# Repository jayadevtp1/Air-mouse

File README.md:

# Air Mouse

Air mouse using Esp32

Four button and a joystick 

mpu6050 

lipo battery charging circuit

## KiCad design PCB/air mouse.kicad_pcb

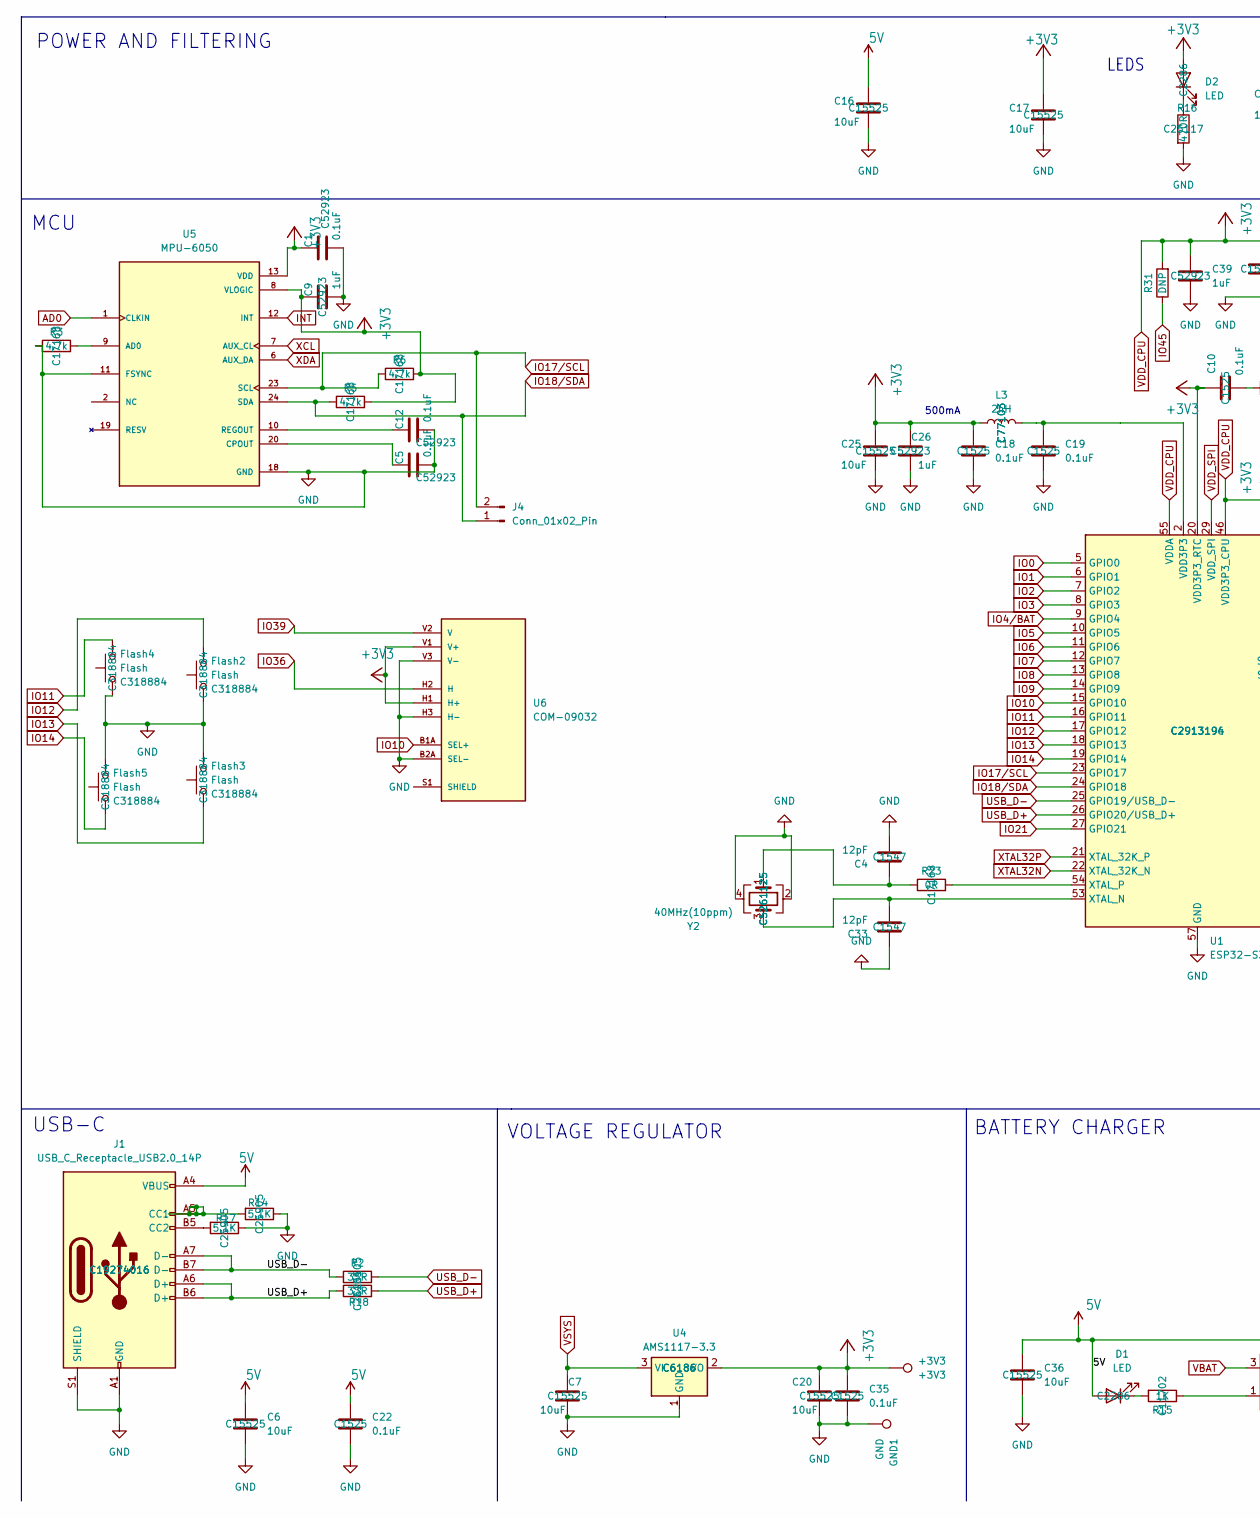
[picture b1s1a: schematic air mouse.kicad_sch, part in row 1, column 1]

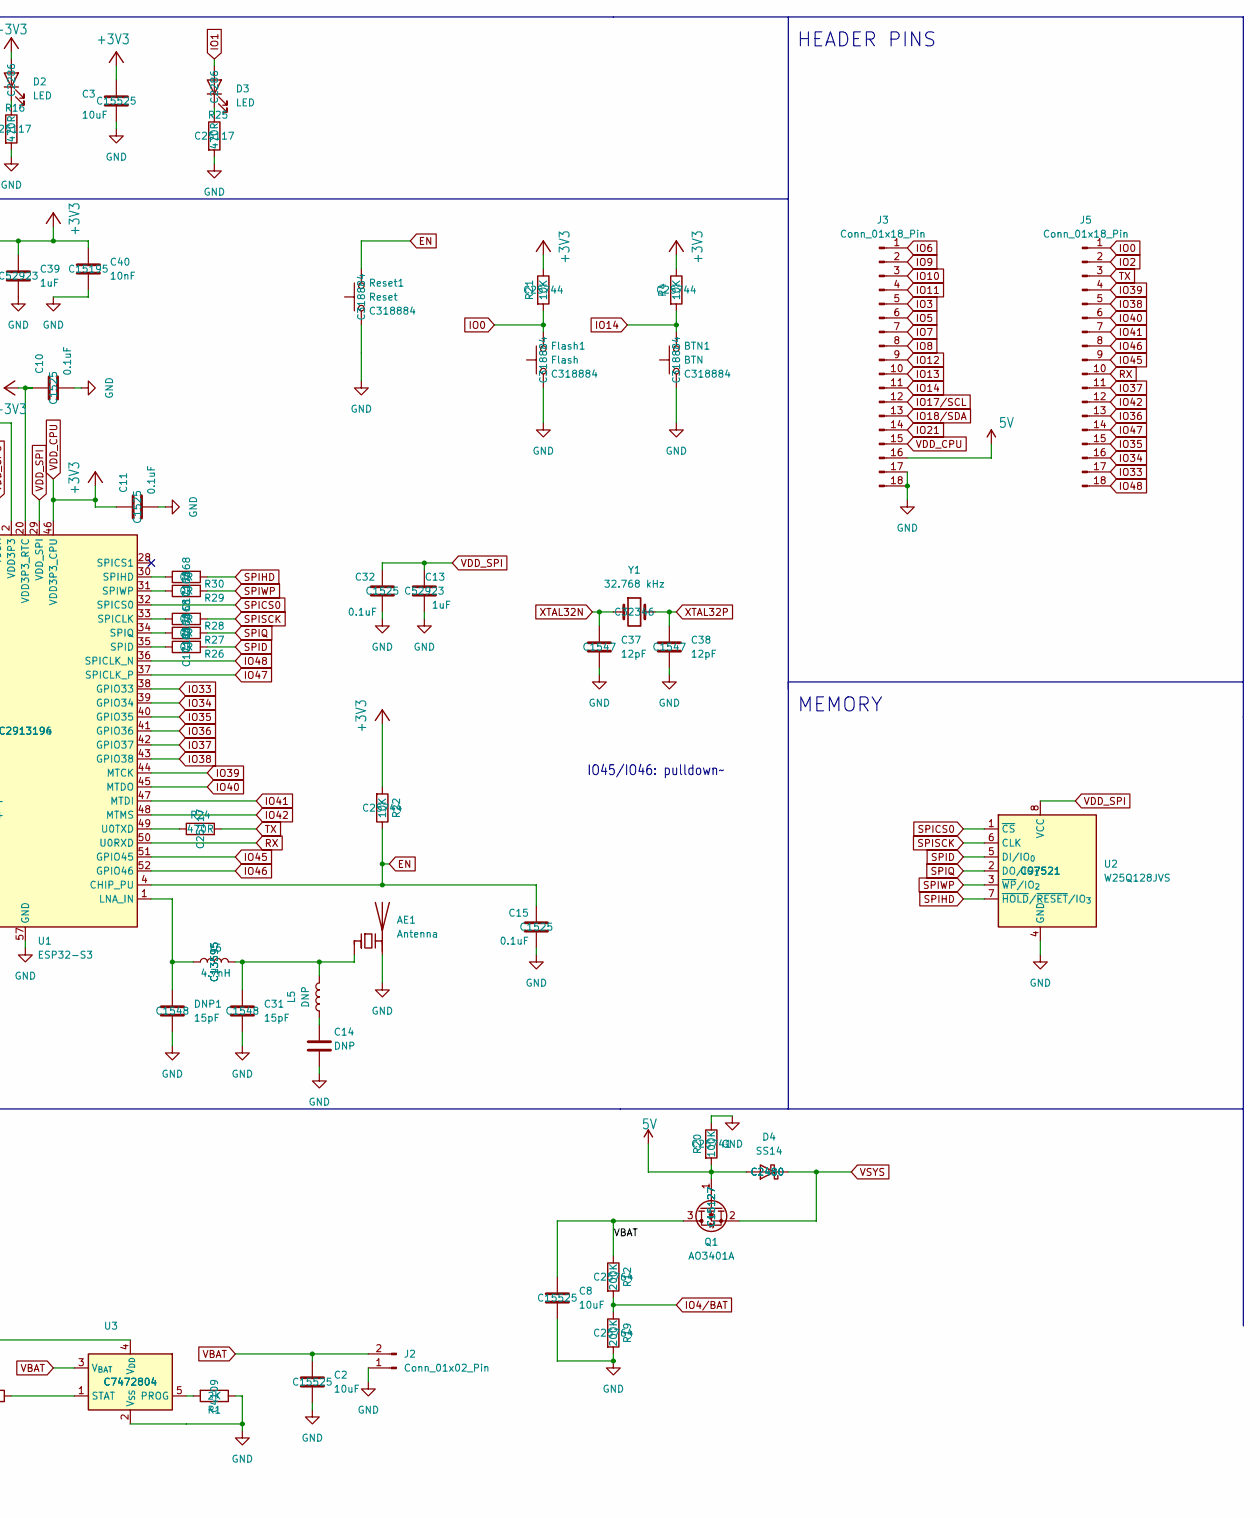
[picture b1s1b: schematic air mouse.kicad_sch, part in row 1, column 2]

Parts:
+3V3: +3V3; TestPoint_Pad_D1.0mm
AE1: Antenna; Texas_SWRA117D_2.4GHz_Left
BTN1: BTN; SW_Push_1P1T_XKB_TS-1187A; MNF PART NUMBER C318884; LCSC C318884
C1, C5, C12: 0.1uF; C_0402_1005Metric; MNF PART NUMBER C52923; LCSC C52923
C2, C3, C6, C7, C8, C16, C17, C20, C25, C36: 10uF; C_0402_1005Metric; MNF PART NUMBER C15525; LCSC C15525
C4, C33, C37, C38: 12pF; C_0402_1005Metric; MNF PART NUMBER C1547; LCSC C1547
C9, C13, C26, C39: 1uF; C_0402_1005Metric; MNF PART NUMBER C52923; LCSC C52923
C10, C11, C15, C18, C19, C22, C32, C35: 0.1uF; C_0402_1005Metric; MNF PART NUMBER C1525; LCSC C1525
C14: DNP; C_0402_1005Metric
C31: 15pF; C_0402_1005Metric; MNF PART NUMBER C1548; LCSC C1548
C40: 10nF; C_0402_1005Metric; MNF PART NUMBER C15195; LCSC C15195
D1, D2, D3: LED; LED_0603_1608Metric; MNF PART NUMBER C2286; LCSC C2286
D4: SS14; D_SMA; MNF PART NUMBER C2480; LCSC C2480
DNP1: 15pF; C_0402_1005Metric; MNF PART NUMBER C1548; LCSC C1548
Flash1, Flash2, Flash3, Flash4, Flash5: Flash; SW_Push_1P1T_XKB_TS-1187A; MNF PART NUMBER C318884; LCSC C318884
GND1: GND; TestPoint_Pad_D1.0mm
J1: USB_C_Receptacle_USB2.0_14P; USB_C_Receptacle_HCTL_HC-TYPE-C-16P-01A; MNF PART NUMBER C19274016; LCSC C19274016
J2, J4: Conn_01x02_Pin; PinSocket_1x02_P2.54mm_Vertical
J3, J5: Conn_01x18_Pin; PinHeader_1x18_P2.54mm_Vertical
L3: 2nH; L_0402_1005Metric; MNF PART NUMBER C77103; LCSC C77103
L5: DNP; L_0402_1005Metric
L6: 4.7nH; L_0402_1005Metric; MNF PART NUMBER C13595; LCSC C13595
Q1: AO3401A; SOT-23; MNF PART NUMBER C15127; LCSC C15127
R1: 2K; R_0402_1005Metric; MNF PART NUMBER C4109; LCSC C4109
R2, R18: 33R; R_0402_1005Metric; MNF PART NUMBER C25105; LCSC C25105
R3, R5, R6: 4.7k; R_0402_1005Metric; MNF PART NUMBER C17168; LCSC C17168
R4, R21, R22: 10K; R_0402_1005Metric; MNF PART NUMBER C25744; LCSC C25744
R12, R19: 200K; R_0402_1005Metric; MNF PART NUMBER C25764; LCSC C25764
R14, R17: 5.1K; R_0402_1005Metric; MNF PART NUMBER C25905; LCSC C25905
R15: 1K; R_0402_1005Metric; MNF PART NUMBER C11702; LCSC C11702
R16, R24, R25: 470R; R_0402_1005Metric; MNF PART NUMBER C25117; LCSC C25117
R20: 100K; R_0402_1005Metric; MNF PART NUMBER C25741; LCSC C25741
R23, R26, R27, R28, R29, R30: 0R; R_0402_1005Metric; MNF PART NUMBER C17168; LCSC C17168
R31: DNP; R_0402_1005Metric
Reset1: Reset; SW_Push_1P1T_XKB_TS-1187A; MNF PART NUMBER C318884; LCSC C318884
U1: ESP32-S3; QFN-56-1EP_7x7mm_P0.4mm_EP4x4mm; MNF PART NUMBER C2913196; LCSC C2913194
U2: W25Q128JVS; SOIC-8_5.3x5.3mm_P1.27mm; MNF PART NUMBER C97521; LCSC C97521
U3: MCP73831-2-OT; SOT-23-5; MNF PART NUMBER C7472804; LCSC C7472804
U4: AMS1117-3.3; SOT-223-3_TabPin2; MNF PART NUMBER C6186; LCSC C6186
U5: MPU-6050; QFN50P400X400X95-24N; PARTREV 3.4
U6: COM-09032; XDCR_COM-09032; PARTREV N/A
Y1: 32.768 kHz; Crystal_SMD_3215-2Pin_3.2x1.5mm; MNF PART NUMBER C32346; LCSC C32346
Y2: 40MHz(10ppm); Crystal_SMD_2520-4Pin_2.5x2.0mm; MNF PART NUMBER C5261125; LCSC C5261125

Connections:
5V: C6.1, C16.1, C22.1, C36.1, D1.2 (A), D4.2 (A), J1.A4 (VBUS), J1.A9 (VBUS), J1.B4 (VBUS), J1.B9 (VBUS), J3.16, Q1.1 (G), R20.2, U3.4 (V_{DD})
AD0: U5.1 (CLKIN)
EN: C15.1, R22.1, Reset1.2, U1.4 (CHIP_PU)
GND: AE1.2 (PCB_Trace), BTN1.1, C1.2, C2.2, C3.2, C4.2, C5.2, C6.2, C7.2, C8.2, C9.2, C10.2, C11.2, C12.2, C13.2, C14.2, C15.2, C16.2, C17.2, C18.2, C19.2, C20.2, C22.2, C25.2, C26.2, C31.2, C32.2, C33.1, C35.2, C36.2, C37.2, C38.2, C39.2, C40.2, DNP1.2, Flash1.1, Flash2.1, Flash3.2, Flash4.1, Flash5.2, GND1.1, J1.A1 (GND), J1.A12 (GND), J1.B1 (GND), J1.B12 (GND), J1.S1 (SHIELD), J2.1, J3.17, J3.18, R1.1, R3.1, R14.1, R16.2, R17.1, R19.2, R20.1, R25.2, Reset1.1, U1.57 (GND), U2.4 (GND), U3.2 (V_{SS}), U4.1 (GND), U5.11 (FSYNC), U5.18 (GND), U6.B2A (SEL-), U6.H3 (H-), U6.V3 (V-), Y2.2, Y2.4
INT: U5.12 (INT)
IO0: Flash1.2, J5.1, R21.2, U1.5 (GPIO0)
IO1: D3.2 (A), U1.6 (GPIO1)
IO2: J5.2, U1.7 (GPIO2)
IO3: J3.5, U1.8 (GPIO3)
IO4/BAT: R12.2, R19.1, U1.9 (GPIO4)
IO5: J3.6, U1.10 (GPIO5)
IO6: J3.1, U1.11 (GPIO6)
IO7: J3.7, U1.12 (GPIO7)
IO8: J3.8, U1.13 (GPIO8)
IO9: J3.2, U1.14 (GPIO9)
IO10: J3.3, U1.15 (GPIO10), U6.B1A (SEL+)
IO11: Flash4.2, J3.4, U1.16 (GPIO11)
IO12: Flash2.2, J3.9, U1.17 (GPIO12)
IO13: Flash3.1, J3.10, U1.18 (GPIO13)
IO14: BTN1.2, Flash5.1, J3.11, R4.2, U1.19 (GPIO14)
IO17/SCL: J3.12, J4.2, R6.1, U1.23 (GPIO17), U5.23 (SCL)
IO18/SDA: J3.13, J4.1, R5.1, U1.24 (GPIO18), U5.24 (SDA)
IO21: J3.14, U1.27 (GPIO21)
IO33: J5.17, U1.38 (GPIO33)
IO34: J5.16, U1.39 (GPIO34)
IO35: J5.15, U1.40 (GPIO35)
IO36: J5.13, U1.41 (GPIO36), U6.H2 (H)
IO37: J5.11, U1.42 (GPIO37)
IO38: J5.5, U1.43 (GPIO38)
IO39: J5.4, U1.44 (MTCK), U6.V2 (V)
IO40: J5.6, U1.45 (MTDO)
IO41: J5.7, U1.47 (MTDI)
IO42: J5.12, U1.48 (MTMS)
IO45: J5.9, R31.1, U1.51 (GPIO45)
IO46: J5.8, U1.52 (GPIO46)
IO47: J5.14, U1.37 (SPICLK_P)
IO48: J5.18, U1.36 (SPICLK_N)
unnamed: AE1.1 (FEED), C31.1, L5.2, L6.2
unnamed: C4.1, R23.1, Y2.1
unnamed: C14.1, L5.1
unnamed: C19.1, L3.2, U1.2 (VDD3P3), U1.3 (VDD3P3)
unnamed: D1.1 (K), R15.2
unnamed: D2.1 (K), R16.1
unnamed: D3.1 (K), R25.1
unnamed: J1.A5 (CC1), R14.2
unnamed: J1.B5 (CC2), R17.2
unnamed: DNP1.1, L6.1, U1.1 (LNA_IN)
unnamed: R28.1, U1.33 (SPICLK)
unnamed: R26.1, U1.35 (SPID)
unnamed: R30.1, U1.30 (SPIHD)
unnamed: R27.1, U1.34 (SPIQ)
unnamed: R29.1, U1.31 (SPIWP)
unnamed: R24.1, U1.49 (U0TXD)
unnamed: C33.2, U1.53 (XTAL_N), Y2.3
unnamed: R23.2, U1.54 (XTAL_P)
unnamed: R1.2, U3.5 (PROG)
unnamed: R15.1, U3.1 (STAT)
unnamed: R3.2, U5.9 (AD0)
unnamed: C5.1, U5.20 (CPOUT)
unnamed: U5.2 (NC), U5.3 (NC), U5.4 (NC), U5.5 (NC), U5.14 (NC), U5.15 (NC), U5.16 (NC), U5.17 (NC)
unnamed: C12.1, U5.10 (REGOUT)
unnamed: U6.S1 (SHIELD), U6.S2 (SHIELD), U6.S3 (SHIELD), U6.S4 (SHIELD)
RX: J5.10, U1.50 (U0RXD)
SPICS0: U1.32 (SPICS0), U2.1 (~CS)
SPID: R26.2, U2.5 (DI/IO_{0})
SPIHD: R30.2, U2.7 (~HOLD/~RESET/IO_{3})
SPIQ: R27.2, U2.2 (DO/IO_{1})
SPISCK: R28.2, U2.6 (CLK)
SPIWP: R29.2, U2.3 (~WP/IO_{2})
TX: J5.3, R24.2
USB_D+: J1.A6 (D+), J1.B6 (D+), R18.1, R18.2, U1.26 (GPIO20/USB_D+)
USB_D-: J1.A7 (D-), J1.B7 (D-), R2.1, R2.2, U1.25 (GPIO19/USB_D-)
VBAT: C2.1, C8.1, J2.2, Q1.3 (D), R12.1, U3.3 (V_{BAT})
VDD_CPU: +3V3.1, C1.1, C3.1, C9.1, C10.1, C11.1, C17.1, C18.1, C20.1, C25.1, C26.1, C35.1, C39.1, C40.1, D2.2 (A), J3.15, L3.1, R4.1, R5.2, R6.2, R21.1, R22.2, R31.2, U1.20 (VDD3P3_RTC), U1.46 (VDD3P3_CPU), U1.55 (VDDA), U1.56 (VDDA), U4.2 (VO), U5.8 (VLOGIC), U5.13 (VDD), U6.H1 (H+), U6.V1 (V+)
VDD_SPI: C13.1, C32.1, U1.29 (VDD_SPI), U2.8 (VCC)
VSYS: C7.1, D4.1 (K), Q1.2 (S), U4.3 (VI)
XCL: U5.7 (AUX_CL)
XDA: U5.6 (AUX_DA)
XTAL32N: C37.1, U1.22 (XTAL_32K_N), Y1.1
XTAL32P: C38.1, U1.21 (XTAL_32K_P), Y1.2

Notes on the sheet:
BATTERY CHARGER
VOLTAGE REGULATOR
500mA
LEDS
MCU
HEADER PINS
MEMORY
POWER AND FILTERING
IO45/IO46: pulldown~~{}
USB-C

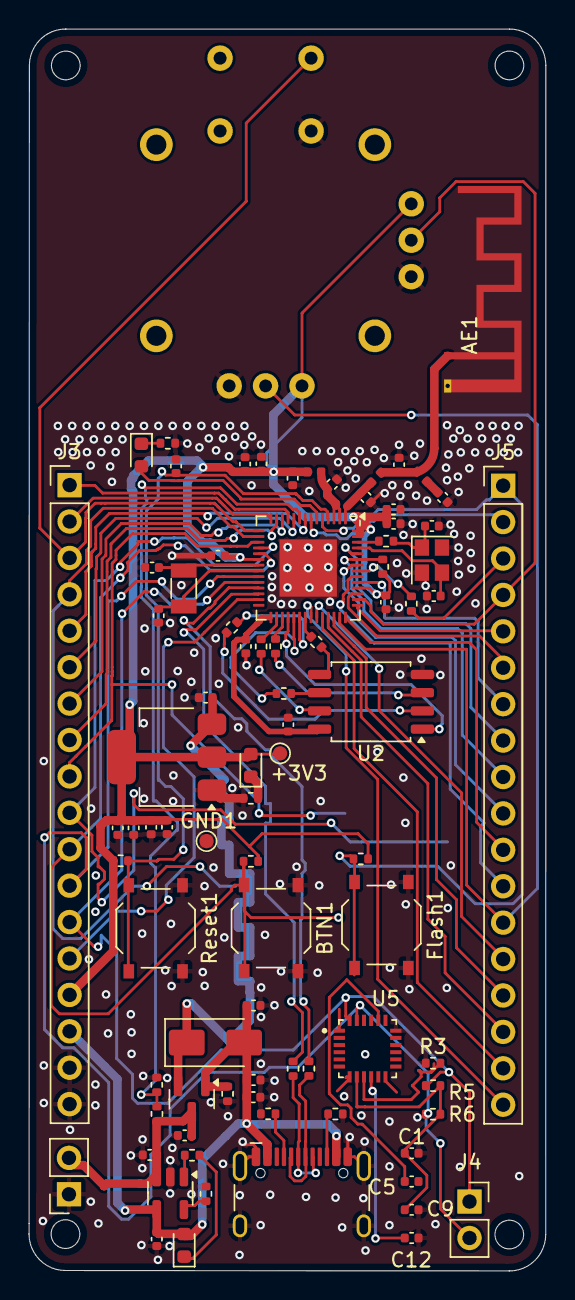
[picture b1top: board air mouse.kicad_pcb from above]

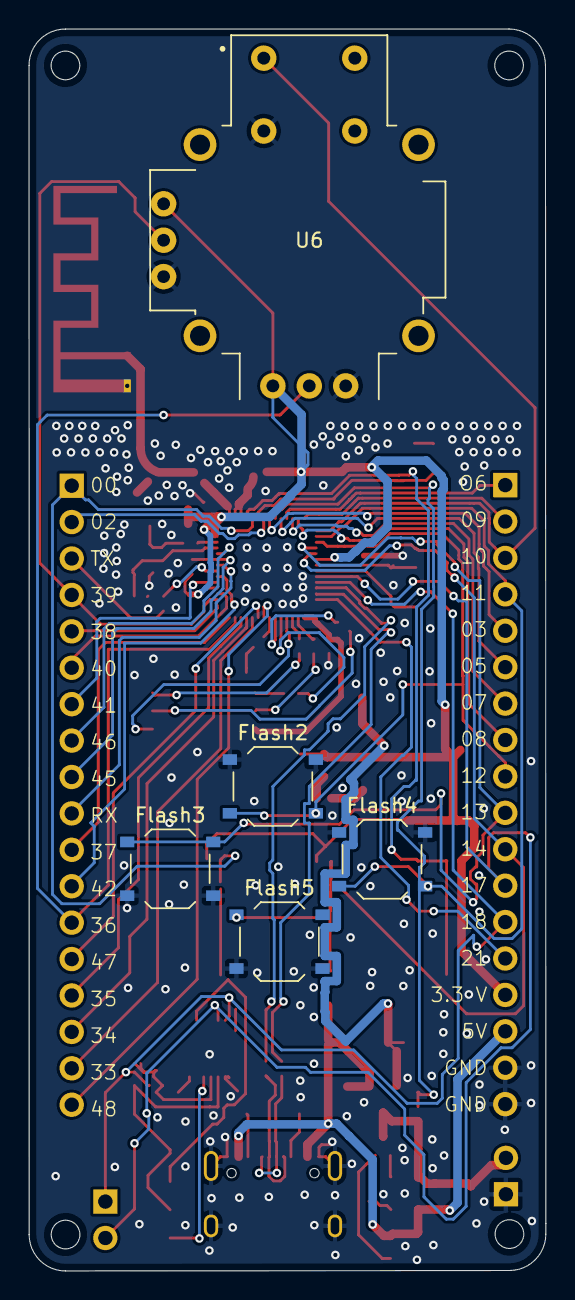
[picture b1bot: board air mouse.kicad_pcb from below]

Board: 2 copper layers, 36.0 x 86.6 mm, 89 parts (5 on the bottom side), 76 nets.

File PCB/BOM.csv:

Comment,Val,Package,Mid X,Mid Y,Rotation,Layer
"BTN1","BTN","SW_Push_1P1T_XKB_TS-1187A","157.8600","-86.0825","-90.0000","top"
"C1","0.1uF","C_0402_1005Metric","167.6680","-101.7860","0.0000","top"
"C2","10uF","C_0402_1005Metric","149.3925","-101.9025","180.0000","top"
"C3","10uF","C_0402_1005Metric","147.1700","-79.0950","-90.0000","top"
"C4","12pF","C_0402_1005Metric","169.0800","-58.0350","0.0000","top"
"C5","0.1uF","C_0402_1005Metric","167.6680","-103.7560","0.0000","top"
"C6","10uF","C_0402_1005Metric","156.6400","-96.6750","0.0000","top"
"C7","10uF","C_0402_1005Metric","153.3000","-70.0000","180.0000","top"
"C8","10uF","C_0402_1005Metric","151.8400","-100.5400","180.0000","top"
"C9","1uF","C_0402_1005Metric","167.6680","-105.7260","0.0000","top"
"C10","0.1uF","C_0402_1005Metric","154.1600","-60.1050","180.0000","top"
"C11","0.1uF","C_0402_1005Metric","165.8800","-63.3550","-90.0000","top"
"C12","0.1uF","C_0402_1005Metric","167.6680","-107.6960","0.0000","top"
"C13","1uF","C_0402_1005Metric","156.1000","-66.4350","-90.0000","top"
"C14","DNP","C_0402_1005Metric","169.8344","-56.0350","-45.0000","top"
"C15","0.1uF","C_0402_1005Metric","151.2350","-53.8575","90.0000","top"
"C16","10uF","C_0402_1005Metric","156.6300","-97.8750","0.0000","top"
"C17","10uF","C_0402_1005Metric","150.6100","-79.0450","-90.0000","top"
"C18","0.1uF","C_0402_1005Metric","159.3700","-54.7050","-90.0000","top"
"C19","0.1uF","C_0402_1005Metric","162.1200","-55.1150","45.0000","top"
"C20","10uF","C_0402_1005Metric","148.2800","-79.0950","-90.0000","top"
"C22","0.1uF","C_0402_1005Metric","156.6400","-91.4750","0.0000","top"
"C25","10uF","C_0402_1005Metric","156.0500","-53.7100","90.0000","top"
"C26","1uF","C_0402_1005Metric","157.1900","-53.6900","90.0000","top"
"C31","15pF","C_0402_1005Metric","166.7915","-53.7550","90.0000","top"
"C32","0.1uF","C_0402_1005Metric","159.0600","-71.8850","90.0000","top"
"C33","12pF","C_0402_1005Metric","169.2100","-62.9150","0.0000","top"
"C35","0.1uF","C_0402_1005Metric","149.5000","-79.0550","-90.0000","top"
"C36","10uF","C_0402_1005Metric","149.8900","-107.7750","-90.0000","top"
"C37","12pF","C_0402_1005Metric","150.0200","-64.2900","-90.0000","top"
"C38","12pF","C_0402_1005Metric","149.5600","-60.9300","180.0000","top"
"C39","1uF","C_0402_1005Metric","166.4100","-56.8750","0.0000","top"
"C40","10nF","C_0402_1005Metric","166.4100","-57.8750","0.0000","top"
"D1","LED","LED_0603_1608Metric","151.8000","-108.2075","90.0000","top"
"D2","LED","LED_0603_1608Metric","156.4500","-74.7275","90.0000","top"
"D3","LED","LED_0603_1608Metric","148.8175","-53.0825","-90.0000","top"
"D4","SS14","D_SMA","153.9800","-94.0650","0.0000","top"
"DNP1","15pF","C_0402_1005Metric","164.4800","-56.0350","-45.0000","top"
"Flash1","Flash","SW_Push_1P1T_XKB_TS-1187A","165.5600","-85.8625","-90.0000","top"
"J1","USB_C_Receptacle_USB2.0_14P","USB_C_Receptacle_HCTL_HC-TYPE-C-16P-01A","160.0100","-105.7750","0.0000","top"
"J2","Conn_01x02_Pin","PinSocket_1x02_P2.54mm_Vertical","143.7640","-104.6480","180.0000","top"
"J3","Conn_01x18_Pin","PinHeader_1x18_P2.54mm_Vertical","143.8100","-55.1800","0.0000","top"
"J4","Conn_01x02_Pin","PinSocket_1x02_P2.54mm_Vertical","171.7040","-105.1560","0.0000","top"
"J5","Conn_01x18_Pin","PinHeader_1x18_P2.54mm_Vertical","174.0500","-55.2200","0.0000","top"
"L3","2nH","L_0402_1005Metric","160.8700","-54.2650","0.0000","top"
"L5","DNP","L_0402_1005Metric","168.3915","-54.5921","135.0000","top"
"L6","4.7nH","L_0402_1005Metric","165.1900","-54.6550","45.0000","top"
"Q1","AO3401A","SOT-23","152.3300","-98.0125","-90.0000","top"
"R1","2K","R_0402_1005Metric","153.3200","-104.6150","-90.0000","top"
"R2","33R","R_0402_1005Metric","160.5000","-95.8800","90.0000","top"
"R3","4.7k","R_0402_1005Metric","169.1640","-95.5040","0.0000","top"
"R4","10K","R_0402_1005Metric","156.4550","-81.4225","180.0000","top"
"R5","4.7k","R_0402_1005Metric","169.1620","-97.0700","0.0000","top"
"R6","4.7k","R_0402_1005Metric","169.1620","-99.0600","0.0000","top"
"R12","200K","R_0402_1005Metric","149.9000","-99.0400","90.0000","top"
"R14","5.1K","R_0402_1005Metric","157.6600","-99.0350","0.0000","top"
"R15","1K","R_0402_1005Metric","152.3525","-101.9225","0.0000","top"
"R16","470R","R_0402_1005Metric","156.4500","-77.0250","180.0000","top"
"R17","5.1K","R_0402_1005Metric","162.3500","-99.0450","180.0000","top"
"R18","33R","R_0402_1005Metric","159.4000","-95.8900","90.0000","top"
"R19","200K","R_0402_1005Metric","149.8900","-97.0100","90.0000","top"
"R20","100K","R_0402_1005Metric","154.8300","-97.6400","90.0000","top"
"R21","10K","R_0402_1005Metric","164.1200","-81.2525","180.0000","top"
"R22","10K","R_0402_1005Metric","147.3700","-81.3825","180.0000","top"
"R23","0R","R_0402_1005Metric","165.8900","-59.0900","180.0000","top"
"R24","470R","R_0402_1005Metric","167.6500","-63.4500","-90.0000","top"
"R25","470R","R_0402_1005Metric","150.6600","-52.2600","0.0000","top"
"R26","0R","R_0402_1005Metric","161.0200","-66.1250","-45.0000","top"
"R27","0R","R_0402_1005Metric","155.1300","-65.1050","-135.0000","top"
"R28","0R","R_0402_1005Metric","158.7500","-69.7150","0.0000","top"
"R29","0R","R_0402_1005Metric","158.1750","-66.4250","-90.0000","top"
"R30","0R","R_0402_1005Metric","157.1700","-66.4350","-90.0000","top"
"R31","DNP","R_0402_1005Metric","165.6500","-60.8750","-90.0000","top"
"Reset1","Reset","SW_Push_1P1T_XKB_TS-1187A","149.8100","-86.0950","-90.0000","top"
"U1","ESP32-S3","QFN-56-1EP_7x7mm_P0.4mm_EP4x4mm","160.4500","-60.9650","-90.0000","top"
"U2","W25Q128JVS","SOIC-8_5.3x5.3mm_P1.27mm","164.8300","-70.2950","180.0000","top"
"U3","MCP73831-2-OT","SOT-23-5","150.8325","-104.5750","-90.0000","top"
"U4","AMS1117-3.3","SOT-223-3_TabPin2","150.5900","-74.1550","180.0000","top"
"U5","MPU-6050","QFN50P400X400X95-24N","164.5920","-94.4880","0.0000","top"
"Y1","32.768_kHz","Crystal_SMD_3215-2Pin_3.2x1.5mm","151.7700","-62.3900","-90.0000","top"
"Y2","40MHz(10ppm)","Crystal_SMD_2520-4Pin_2.5x2.0mm","169.0800","-60.4100","-90.0000","top"
"Flash2","Flash","SW_Push_1P1T_XKB_TS-1187A","160.0200","-76.2000","180.0000","bottom"
"Flash3","Flash","SW_Push_1P1T_XKB_TS-1187A","167.1800","-81.9450","180.0000","bottom"
"Flash4","Flash","SW_Push_1P1T_XKB_TS-1187A","152.4000","-81.2800","180.0000","bottom"
"Flash5","Flash","SW_Push_1P1T_XKB_TS-1187A","159.5600","-87.0250","180.0000","bottom"
"U6","COM-09032","XDCR_COM-09032","157.4800","-38.1000","180.0000","bottom"
